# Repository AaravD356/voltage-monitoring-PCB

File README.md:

### UMD Mars Rover Electrical Team

### Voltage Monitoring PCB
This project involves a custom PCB designed to monitor the voltage of a multi-cell battery pack and transmit the readings over a CAN bus. The core of the system is an STM32 microcontroller, which reads the voltage of each cell through voltage divider circuits. The measured values are then transmitted via a SN65HVD230 CAN transceiver to a Jetson Nano, which acts as the receiver and processor.

### System Overview
The PCB includes six voltage divider circuits, one for each battery cell, to scale down the cell voltages to a level readable by the STM32's ADC inputs. The STM32 continuously reads these voltages and formats the data into a CAN message. The SN65HVD230 transceiver handles communication over the CAN bus, ensuring reliable data transfer to the Jetson Nano or any compatible receiver.

### CAN Communication
Each CAN message contains the measured voltages, formatted as an array of 16-bit unsigned integers representing millivolts. A static CAN ID is used to identify messages from the monitoring board. This ID can be customized in the STM32 firmware if needed.

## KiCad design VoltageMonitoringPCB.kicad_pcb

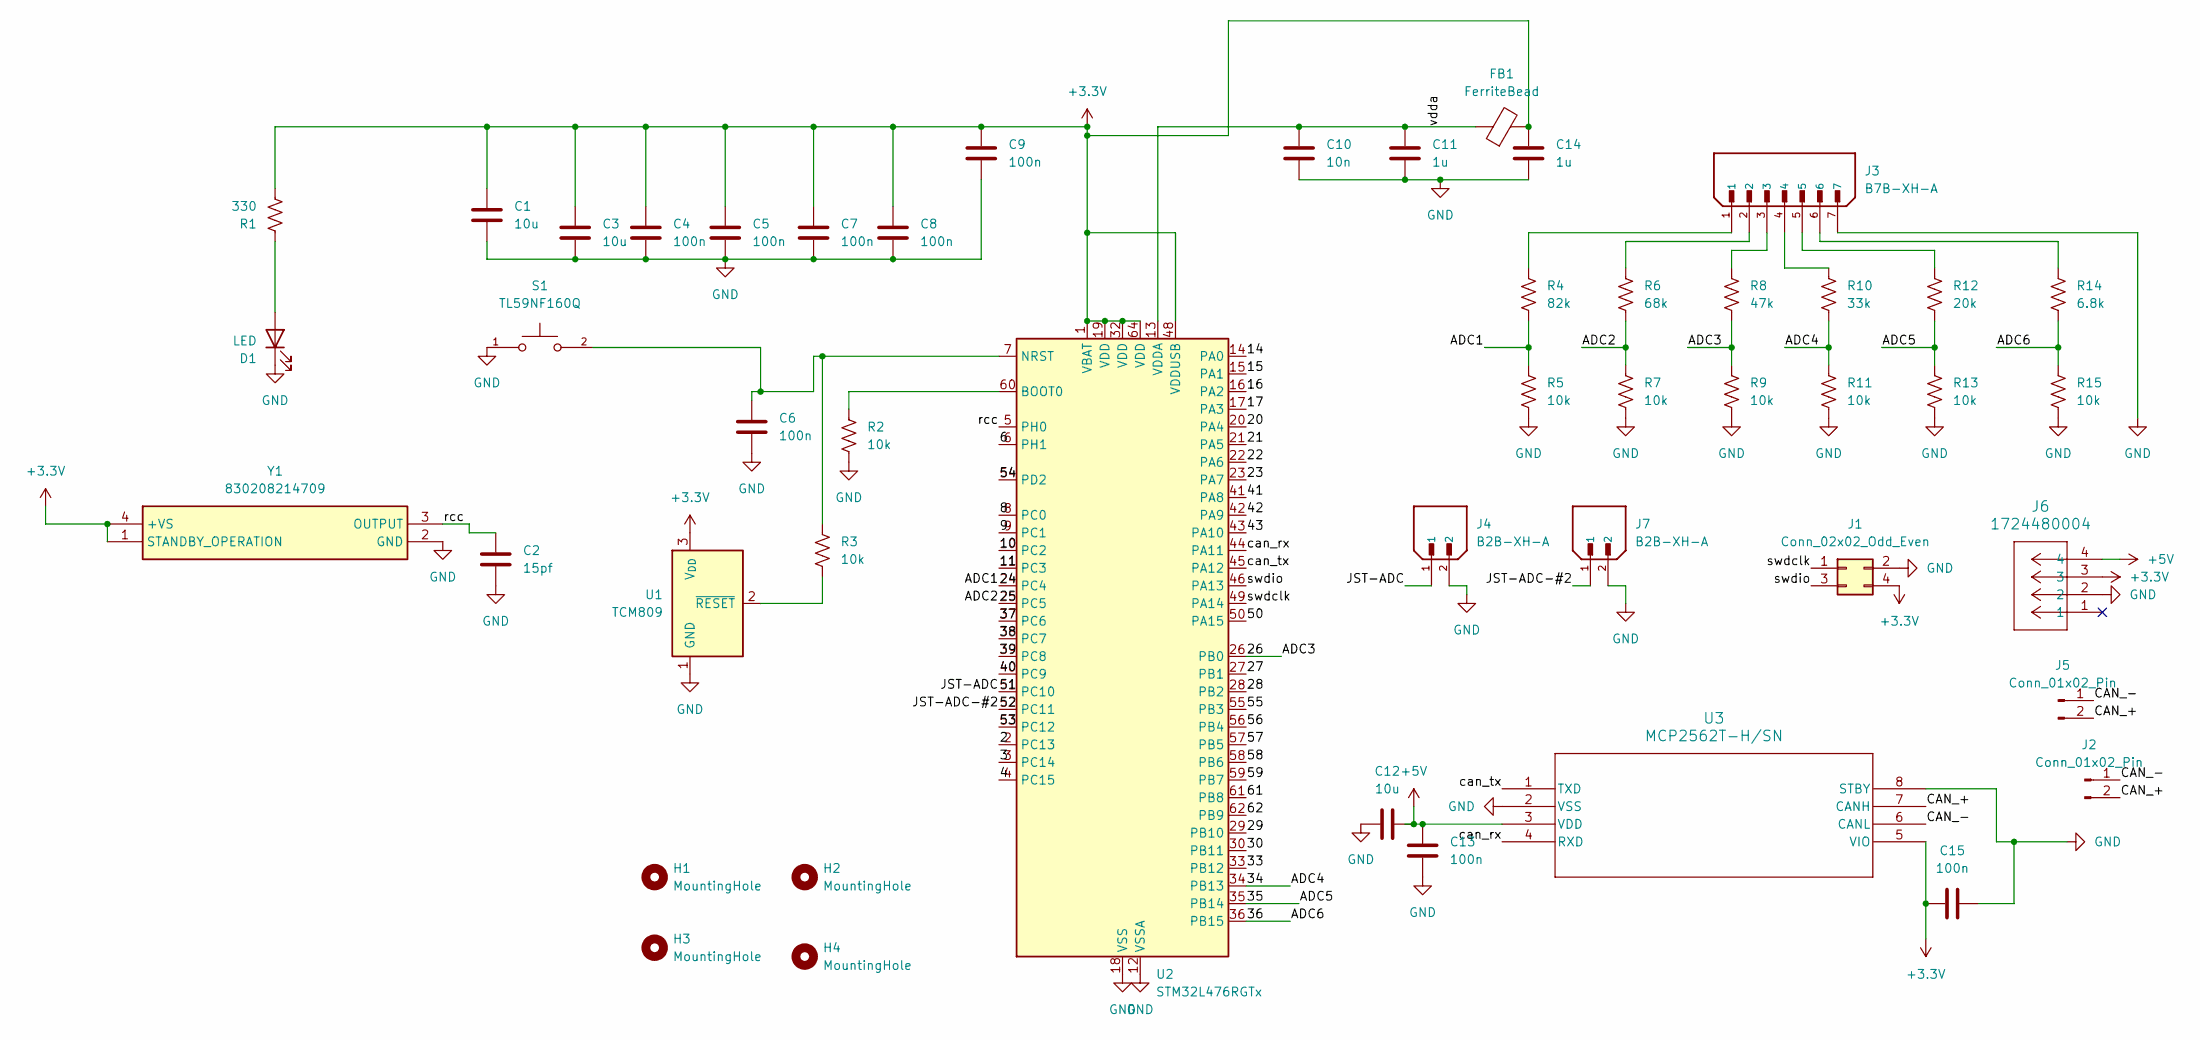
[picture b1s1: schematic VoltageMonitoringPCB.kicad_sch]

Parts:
C1, C3, C12: 10u; C_0805_2012Metric_Pad1.18x1.45mm_HandSolder
C2: 15pf; 15pf_cap
C4, C5, C6, C7, C8, C9, C13, C15: 100n; C_0805_2012Metric_Pad1.18x1.45mm_HandSolder
C10: 10n; C_0805_2012Metric_Pad1.18x1.45mm_HandSolder
C11, C14: 1u; C_0402_1005Metric_Pad0.74x0.62mm_HandSolder
D1: LED; small_led
FB1: FerriteBead; ferrite_bead02BH1J
H1, H2, H3, H4: MountingHole
J1: Conn_02x02_Odd_Even; PinHeader_2x02_P2.54mm_Vertical
J2, J5: Conn_01x02_Pin; can_molex_header
J3: B7B-XH-A; 7-PinJST-ad; PARTREV 7/4/21
J4, J7: B2B-XH-A; 2-PinJST-ad; PARTREV N/A
J6: 1724480004; power_header
R1: 330; R_0805_2012Metric_Pad1.20x1.40mm_HandSolder
R2, R3, R5, R7, R9, R11, R13, R15: 10k; R_0402_1005Metric_Pad0.72x0.64mm_HandSolder
R4: 82k; 82kOhmRes-ad
R6: 68k; 68kOhmRes-ad
R8: 47k; 47kOhmRes-ad
R10: 33k; 33kOhmRes-ad
R12: 20k; 20kOhmRes-ad
R14: 6.8k; 6.8kOhmRes-ad
S1: TL59NF160Q; reset_button; PARTREV G
U1: TCM809; SOT-23_Handsoldering
U2: STM32L476RGTx; LQFP-64_10x10mm_P0.5mm
U3: MCP2562T-H/SN; can_transceiver
Y1: 830208214709; oscillator; Mouser Part Number 710-830208214709

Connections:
+3.3V: C1.1, C3.1, C4.1, C5.1, C7.1, C8.1, C9.1, C14.1, C15.1, FB1.2, J1.4, J6.3, R1.2, U1.3 (V_{DD}), U2.1 (VBAT), U2.19 (VDD), U2.32 (VDD), U2.48 (VDDUSB), U2.64 (VDD), U3.5 (VIO), Y1.1 (STANDBY_OPERATION), Y1.4 (+VS)
+5V: C12.2, C13.2, J6.4, U3.3 (VDD)
/2: U2.2 (PC13)
/3: U2.3 (PC14)
/4: U2.4 (PC15)
/6: U2.6 (PH1)
/8: U2.8 (PC0)
/9: U2.9 (PC1)
/10: U2.10 (PC2)
/11: U2.11 (PC3)
/14: U2.14 (PA0)
/15: U2.15 (PA1)
/16: U2.16 (PA2)
/17: U2.17 (PA3)
/20: U2.20 (PA4)
/21: U2.21 (PA5)
/22: U2.22 (PA6)
/23: U2.23 (PA7)
/24: R4.2, R5.1, U2.24 (PC4)
/25: R6.2, R7.1, U2.25 (PC5)
/26: R8.2, R9.1, U2.26 (PB0)
/27: U2.27 (PB1)
/28: U2.28 (PB2)
/29: U2.29 (PB10)
/30: U2.30 (PB11)
/33: U2.33 (PB12)
/34: R10.2, R11.1, U2.34 (PB13)
/35: R12.2, R13.1, U2.35 (PB14)
/36: R14.2, R15.1, U2.36 (PB15)
/37: U2.37 (PC6)
/38: U2.38 (PC7)
/39: U2.39 (PC8)
/40: U2.40 (PC9)
/41: U2.41 (PA8)
/42: U2.42 (PA9)
/43: U2.43 (PA10)
/50: U2.50 (PA15)
/51: J4.1, U2.51 (PC10)
/52: J7.1, U2.52 (PC11)
/53: U2.53 (PC12)
/54: U2.54 (PD2)
/55: U2.55 (PB3)
/56: U2.56 (PB4)
/57: U2.57 (PB5)
/58: U2.58 (PB6)
/59: U2.59 (PB7)
/61: U2.61 (PB8)
/62: U2.62 (PB9)
/CAN_+: J2.2, J5.2, U3.7 (CANH)
/CAN_-: J2.1, J5.1, U3.6 (CANL)
/can_rx: U2.44 (PA11), U3.4 (RXD)
/can_tx: U2.45 (PA12), U3.1 (TXD)
/rcc: C2.1, U2.5 (PH0), Y1.3 (OUTPUT)
/swdclk: J1.1, U2.49 (PA14)
/swdio: J1.3, U2.46 (PA13)
/vdda: C10.1, C11.1, FB1.1, U2.13 (VDDA)
GND: C1.2, C2.2, C3.2, C4.2, C5.2, C6.2, C7.2, C8.2, C9.2, C10.2, C11.2, C12.1, C13.1, C14.2, C15.2, D1.1 (K), J1.2, J3.7, J4.2, J6.2, J7.2, R2.2, R5.2, R7.2, R9.2, R11.2, R13.2, R15.2, S1.1, U1.1 (GND), U2.12 (VSSA), U2.18 (VSS), U2.31 (VSS), U2.47 (VSS), U2.63 (VSS), U3.2 (VSS), U3.8 (STBY), Y1.2 (GND)
unnamed: D1.2 (A), R1.1
unnamed: J3.1, R4.1
unnamed: J3.2, R6.1
unnamed: J3.3, R8.1
unnamed: J3.4, R10.1
unnamed: J3.5, R12.1
unnamed: J3.6, R14.1
unnamed: R3.2, U1.2 (~RESET)
unnamed: R2.1, U2.60 (BOOT0)
unnamed: C6.1, R3.1, S1.2, U2.7 (NRST)

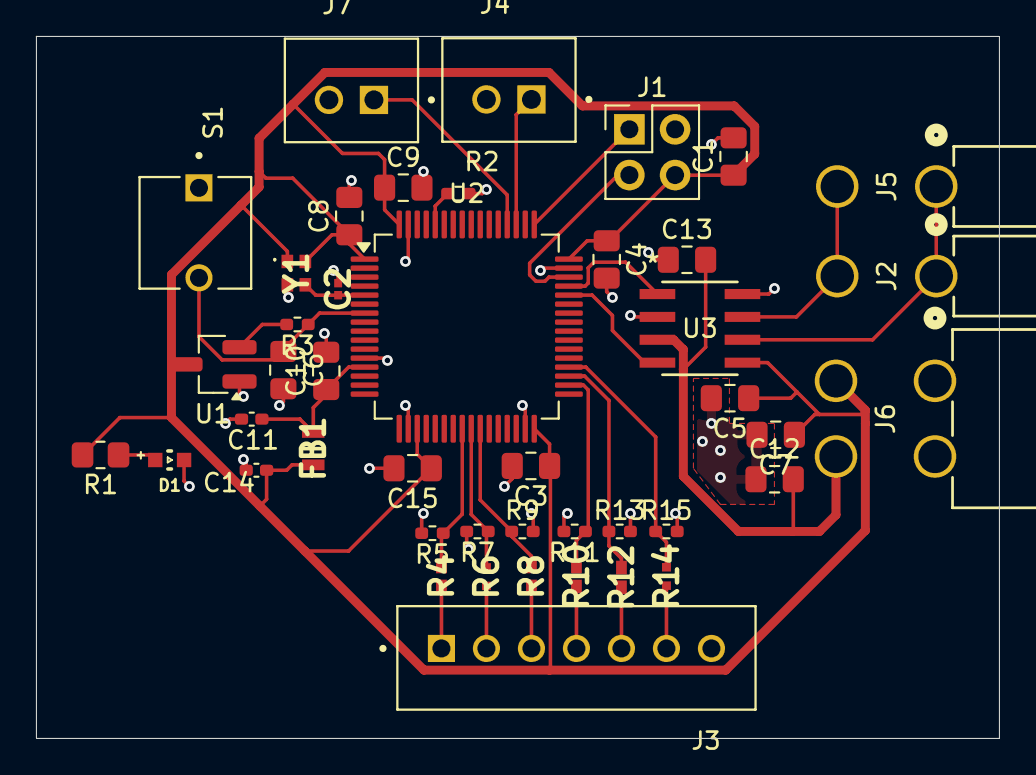
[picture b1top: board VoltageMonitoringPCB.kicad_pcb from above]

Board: 2 copper layers, 53.5 x 39.0 mm, 44 parts (0 on the bottom side), 29 nets.

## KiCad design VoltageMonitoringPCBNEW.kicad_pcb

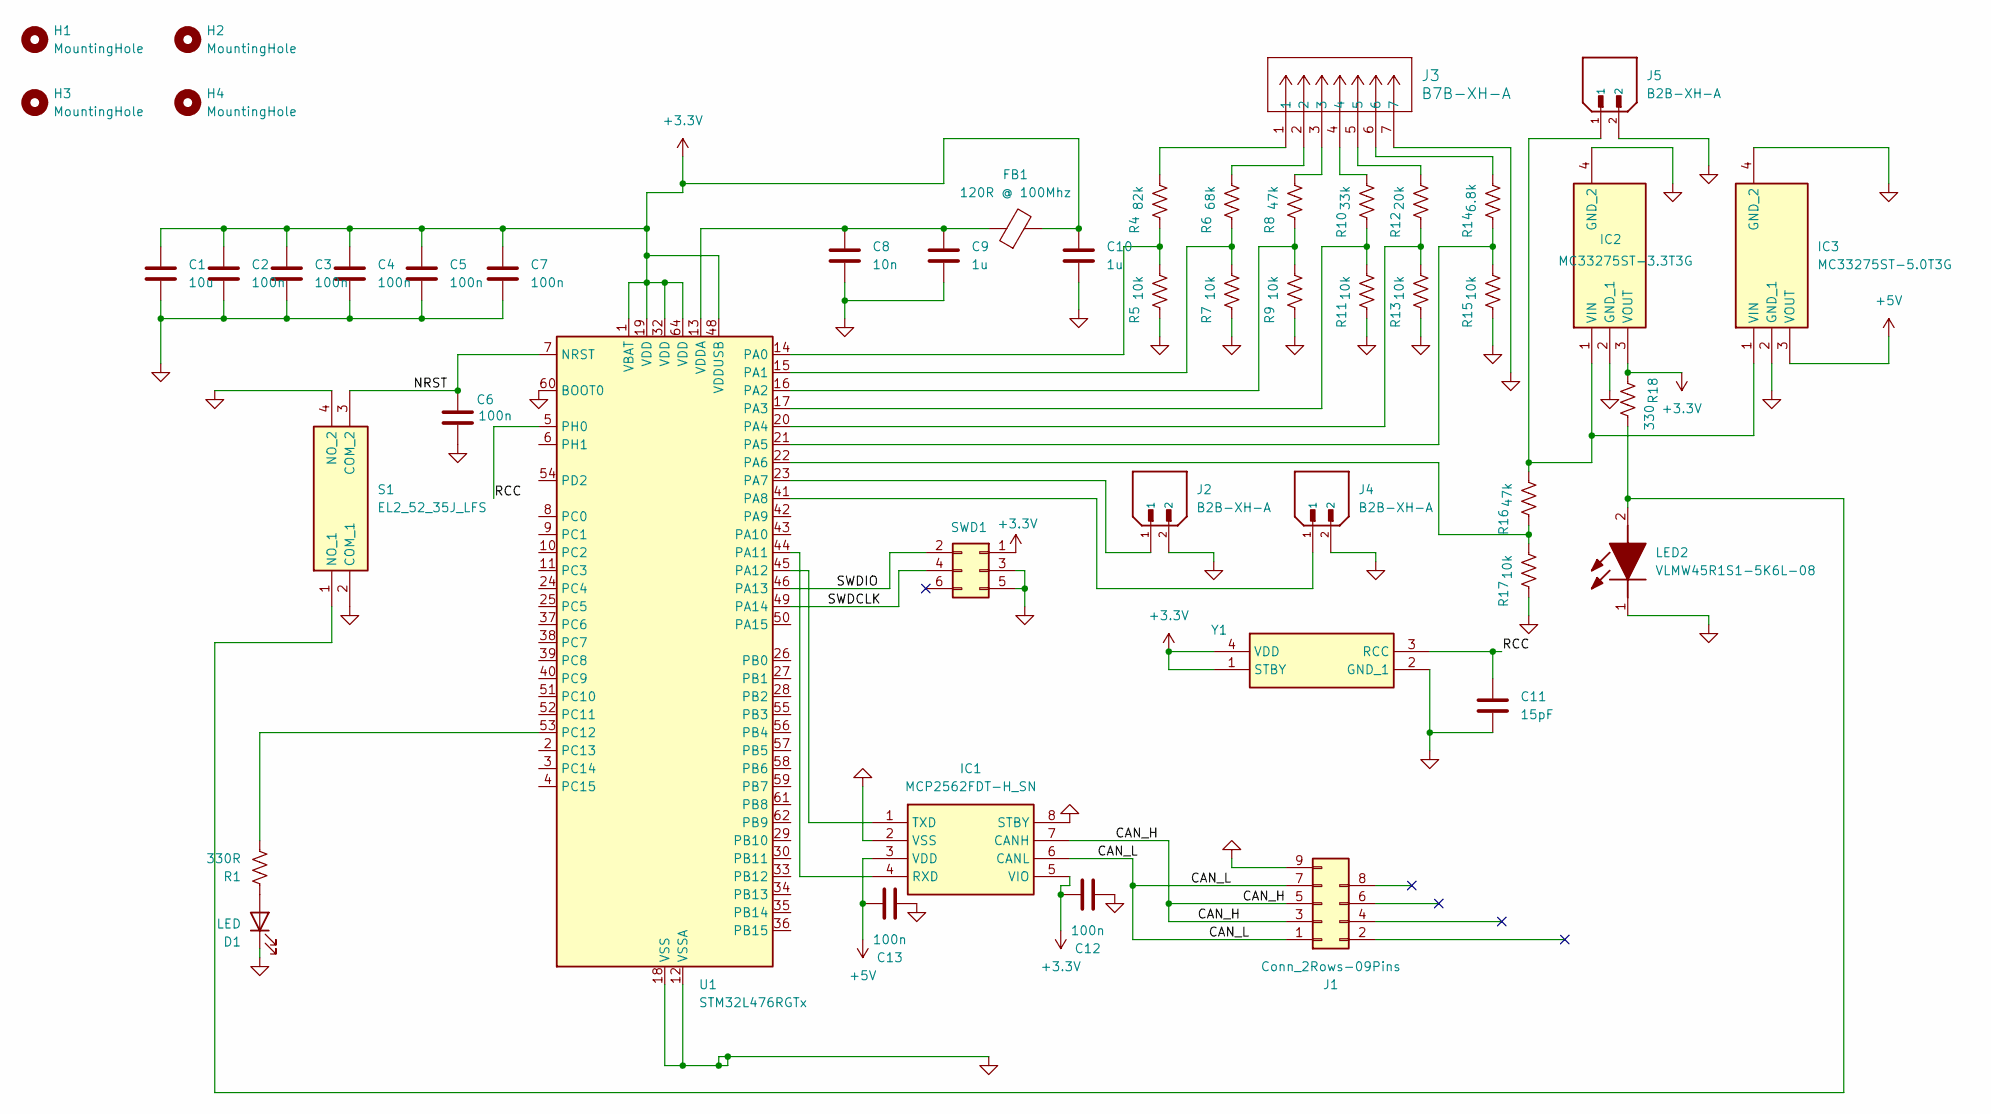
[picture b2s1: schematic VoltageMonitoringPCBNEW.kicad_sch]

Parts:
C1: 10u; CAPC3216X94N
C2, C3, C4, C5, C6, C7, C12, C13: 100n; CAPC2012X94N
C8: 10n; CAPC2012X94N
C9, C10: 1u; CAPC1005X55N
C11: 15pF; EZJP0V180HA
D1: LED; LEDM3528X185N
FB1: 120R @ 100Mhz; BLM21AG102BH1J
H1, H2, H3, H4: MountingHole; MountingHole_3.2mm_M3
IC1: MCP2562FDT-H_SN; SOIC127P600X175-8N; Manufacturer_Part_Number MCP2562FDT-H/SN; Mouser Part Number 579-MCP2562FDT-H/SN
IC2: MC33275ST-3.3T3G; SOT230P700X180-4N; Mouser Part Number 863-MC33275ST-3.3T3G
IC3: MC33275ST-5.0T3G; SOT230P700X180-4N5v; Mouser Part Number 863-MC33275ST-5.0T3G
J1: Conn_2Rows-09Pins; CONN9X1_2286550-1_TEC
J2, J4, J5: B2B-XH-A; JST_B2B-XH-A; PARTREV N/A
J3: B7B-XH-A; CONN_B7B-XH-A_JST
LED2: VLMW45R1S1-5K6L-08; LEDM3528X185N; Mouser Part Number 78-VLMW45R1S1-5K6L08
R1: 330R; RESC2012X55N
R4: 82k; RESC2012X70N
R5, R7, R9, R11, R13, R15, R17: 10k; RESC1005X45N
R6: 68k; ERJUP6
R8: 47k; ERA3AEB101V
R10: 33k; RESC6432X65N
R12: 20k; ERA6AEB101V
R14: 6.8k; RESC2012X60N6.8K
R16: 47k; RESC2012X60N
R18: 330; RESC2012X55N
S1: EL2_52_35J_LFS; EL25235JLFS; Manufacturer_Part_Number EL2 52 35J LFS
SWD1: Conn_02x03_Odd_Even; HDRV6W82P254_2X3_762X500X884P
U1: STM32L476RGTx; LQFP-64_10x10mm_P0.5mm
Y1: ABM11-16.000MHz-D2X-T; 830208214709; Manufacturer_Part_Number ABM11-16.000MHz-D2X-T; Mouser Part Number 815-BM1116000MHZD2XT

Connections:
+3.3V: C1.1, C2.1, C3.1, C4.1, C5.1, C7.1, C10.1, C12.1, FB1.2, IC1.5 (VIO), IC2.3 (VOUT), R18.2, SWD1.1, U1.1 (VBAT), U1.19 (VDD), U1.32 (VDD), U1.48 (VDDUSB), U1.64 (VDD), Y1.1 (STBY), Y1.4 (VDD)
+5V: C13.2, IC1.3 (VDD), IC3.3 (VOUT)
/CAN_H: IC1.7 (CANH), J1.3, J1.5
/CAN_L: IC1.6 (CANL), J1.1, J1.7
/NRST: C6.1, S1.3 (COM_2), U1.7 (NRST)
/RCC: C11.1, U1.5 (PH0), Y1.3 (RCC)
/SWDCLK: SWD1.4, U1.49 (PA14)
/SWDIO: SWD1.2, U1.46 (PA13)
GND: C1.2, C2.2, C3.2, C4.2, C5.2, C6.2, C7.2, C8.2, C9.2, C10.2, C11.2, C12.2, C13.1, D1.1 (K), IC1.2 (VSS), IC1.8 (STBY), IC2.2 (GND_1), IC2.4 (GND_2), IC3.2 (GND_1), IC3.4 (GND_2), J1.9, J2.2, J3.7, J4.2, J5.2, LED2.1 (K), R5.1, R7.1, R9.1, R11.1, R13.1, R15.1, R17.1, S1.2 (COM_1), S1.4 (NO_2), SWD1.3, SWD1.5, U1.12 (VSSA), U1.18 (VSS), U1.31 (VSS), U1.47 (VSS), U1.60 (BOOT0), U1.63 (VSS), Y1.2 (GND_1)
unnamed: D1.2 (A), R1.1
unnamed: IC1.4 (RXD), U1.44 (PA11)
unnamed: IC1.1 (TXD), U1.45 (PA12)
unnamed: IC2.1 (VIN), IC3.1 (VIN), J5.1, R16.2
unnamed: J3.1, R4.2
unnamed: J3.2, R6.2
unnamed: J3.3, R8.2
unnamed: J3.4, R10.2
unnamed: J3.5, R12.2
unnamed: J3.6, R14.2
unnamed: LED2.2 (A), R18.1, S1.1 (NO_1)
unnamed: R4.1, R5.2, U1.14 (PA0)
unnamed: R6.1, R7.2, U1.15 (PA1)
unnamed: R8.1, R9.2, U1.16 (PA2)
unnamed: R10.1, R11.2, U1.17 (PA3)
unnamed: R12.1, R13.2, U1.20 (PA4)
unnamed: R14.1, R15.2, U1.21 (PA5)
unnamed: R16.1, R17.2, U1.22 (PA6)
unnamed: J2.1, U1.23 (PA7)
unnamed: J4.1, U1.41 (PA8)
unnamed: R1.2, U1.53 (PC12)
unnamed: C8.1, C9.1, FB1.1, U1.13 (VDDA)

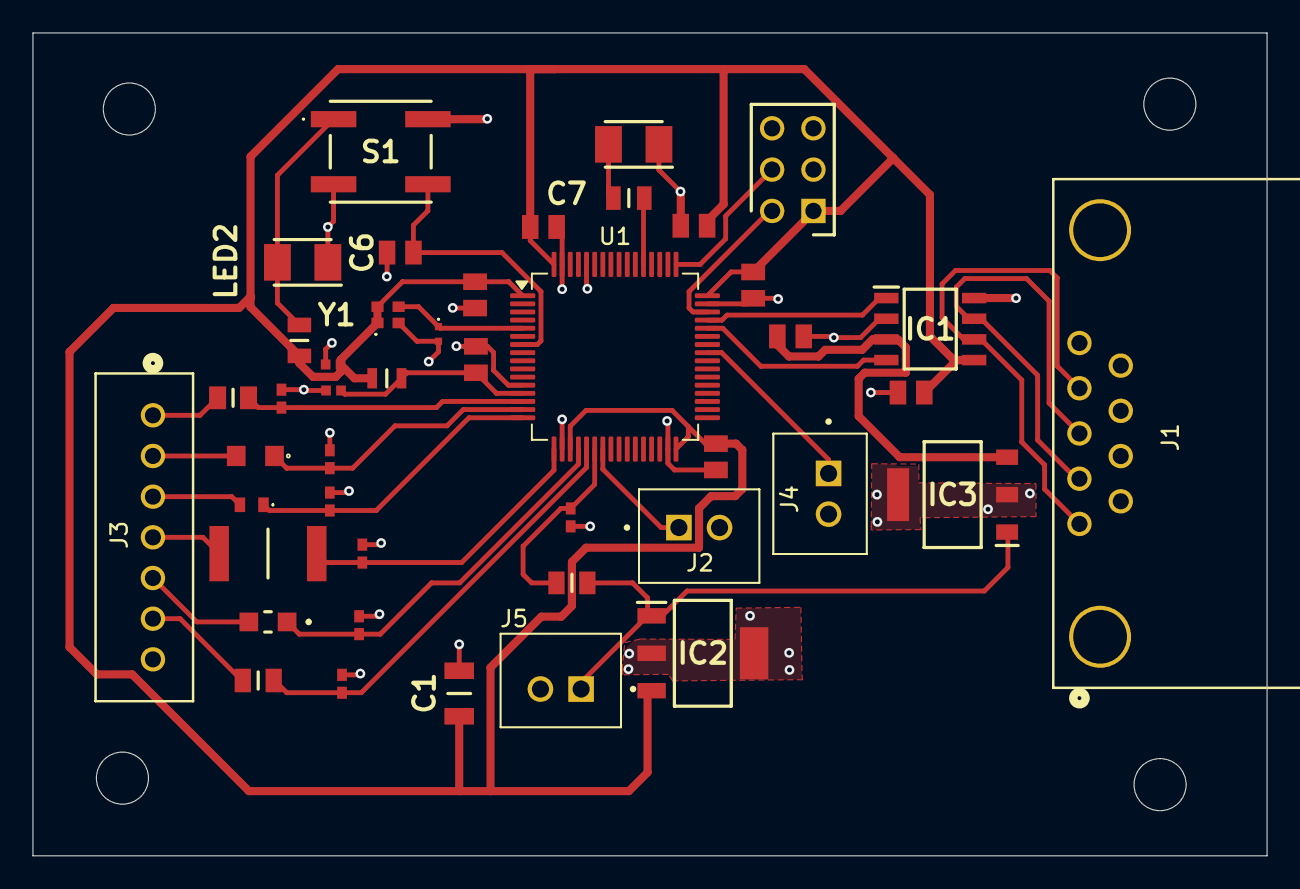
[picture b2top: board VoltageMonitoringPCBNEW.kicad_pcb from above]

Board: 2 copper layers, 75.9 x 50.6 mm, 48 parts (0 on the bottom side), 31 nets.

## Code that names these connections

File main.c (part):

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  * @file           : main.c
  * @brief          : Voltage monitor + CAN + fault detection (STM32L476 + MCP2562)
  * @note           : 6 isolated cell voltage readings, ADC1..ADC6:
  *                   - ADC1: PC4  (ADC1_IN14)  82k/10k
  *                   - ADC2: PC5  (ADC1_IN15)  68k/10k
  *                   - ADC3: PB0  (ADC1_IN8)   47k/10k
  *                   - ADC4: PB13 (ADC1_IN5)   33k/10k
  *                   - ADC5: PB14 (ADC1_IN6)   20k/10k
  *                   - ADC6: PB15 (ADC1_IN7)    6.8k/10k
  *
  *                   Relay JST connectors: PC10, PC11 (initialized, unused)
  *                   MCP2562 STBY: PB2 (LOW = normal)
  ******************************************************************************
  */
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
// ADC scan order indices
enum {
  CH_ADC1 = 0, // PC4
  CH_ADC2,     // PC5
  CH_ADC3,     // PB0
  CH_ADC4,     // PB13
  CH_ADC5,     // PB14
  CH_ADC6      // PB15
};

// Divider gains (Rtop+Rbot)/Rbot
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
/* =================== CubeMX Init Stubs =================== */
/* Configure ADC ranks in CubeMX:
   Rank1: PC4  (ADC1_IN14)
   Rank2: PC5  (ADC1_IN15)
   Rank3: PB0  (ADC1_IN8)
   Rank4: PB13 (ADC1_IN5)
   Rank5: PB14 (ADC1_IN6)
   Rank6: PB15 (ADC1_IN7)
   DMA: Circular, half-word
*/
/* =================== CubeMX Init Stubs / Minimal implementations =================== */
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  }

  /* Configure regular channels in the same order as the DMA buffer expects */
  /* Rank 1: PC4  -> ADC_CHANNEL_14 */
  sConfig.Channel = ADC_CHANNEL_14;
  sConfig.Rank = ADC_REGULAR_RANK_1;
  sConfig.SamplingTime = ADC_SAMPLETIME_247CYCLES_5; // long sample for high impedance dividers
  if (HAL_ADC_ConfigChannel(&hadc1, &sConfig) != HAL_OK) Error_Handler();

  /* Rank 2: PC5 -> ADC_CHANNEL_15 */
  sConfig.Channel = ADC_CHANNEL_15;
  sConfig.Rank = ADC_REGULAR_RANK_2;
  if (HAL_ADC_ConfigChannel(&hadc1, &sConfig) != HAL_OK) Error_Handler();

  /* Rank 3: PB0 -> ADC_CHANNEL_8 */
  sConfig.Channel = ADC_CHANNEL_8;
  sConfig.Rank = ADC_REGULAR_RANK_3;
  if (HAL_ADC_ConfigChannel(&hadc1, &sConfig) != HAL_OK) Error_Handler();

  /* Rank 4: PB13 -> ADC_CHANNEL_5 */
  sConfig.Channel = ADC_CHANNEL_5;
  sConfig.Rank = ADC_REGULAR_RANK_4;
  if (HAL_ADC_ConfigChannel(&hadc1, &sConfig) != HAL_OK) Error_Handler();

  /* Rank 5: PB14 -> ADC_CHANNEL_6 */
  sConfig.Channel = ADC_CHANNEL_6;
  sConfig.Rank = ADC_REGULAR_RANK_5;
  if (HAL_ADC_ConfigChannel(&hadc1, &sConfig) != HAL_OK) Error_Handler();

  /* Rank 6: PB15 -> ADC_CHANNEL_7 */
  sConfig.Channel = ADC_CHANNEL_7;
  sConfig.Rank = ADC_REGULAR_RANK_6;
  if (HAL_ADC_ConfigChannel(&hadc1, &sConfig) != HAL_OK) Error_Handler();
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
/**
  * @brief GPIO Initialization Function
  * @note Initializes pins used in firmware: CAN STBY (PB2), Relay JST pins (PC10, PC11).
  *       CubeMX will also configure PA11/PA12 for CAN AF and pull settings.
  */
static void MX_GPIO_Init(void)
{
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  GPIO_InitStruct.Speed = GPIO_SPEED_FREQ_LOW;
  HAL_GPIO_Init(CAN_STBY_GPIO_Port, &GPIO_InitStruct);

  /* Relay JST outputs (PC10, PC11) as general outputs (unused by firmware now) */
  HAL_GPIO_WritePin(RELAY1_GPIO_Port, RELAY1_Pin, GPIO_PIN_RESET);
  HAL_GPIO_WritePin(RELAY2_GPIO_Port, RELAY2_Pin, GPIO_PIN_RESET);

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  GPIO_InitStruct.Speed = GPIO_SPEED_FREQ_LOW;
  HAL_GPIO_Init(RELAY1_GPIO_Port, &GPIO_InitStruct);

  /* Note: CAN TX/RX pins (PA12/PA11) alternate function config normally generated by CubeMX */
}

/* Error handler */
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
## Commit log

2025-07-18 README.md
